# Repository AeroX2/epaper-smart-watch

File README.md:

# E-paper smart watch

- [Watch firmware](code/README.md)
- [Android companion](companion/README.md)

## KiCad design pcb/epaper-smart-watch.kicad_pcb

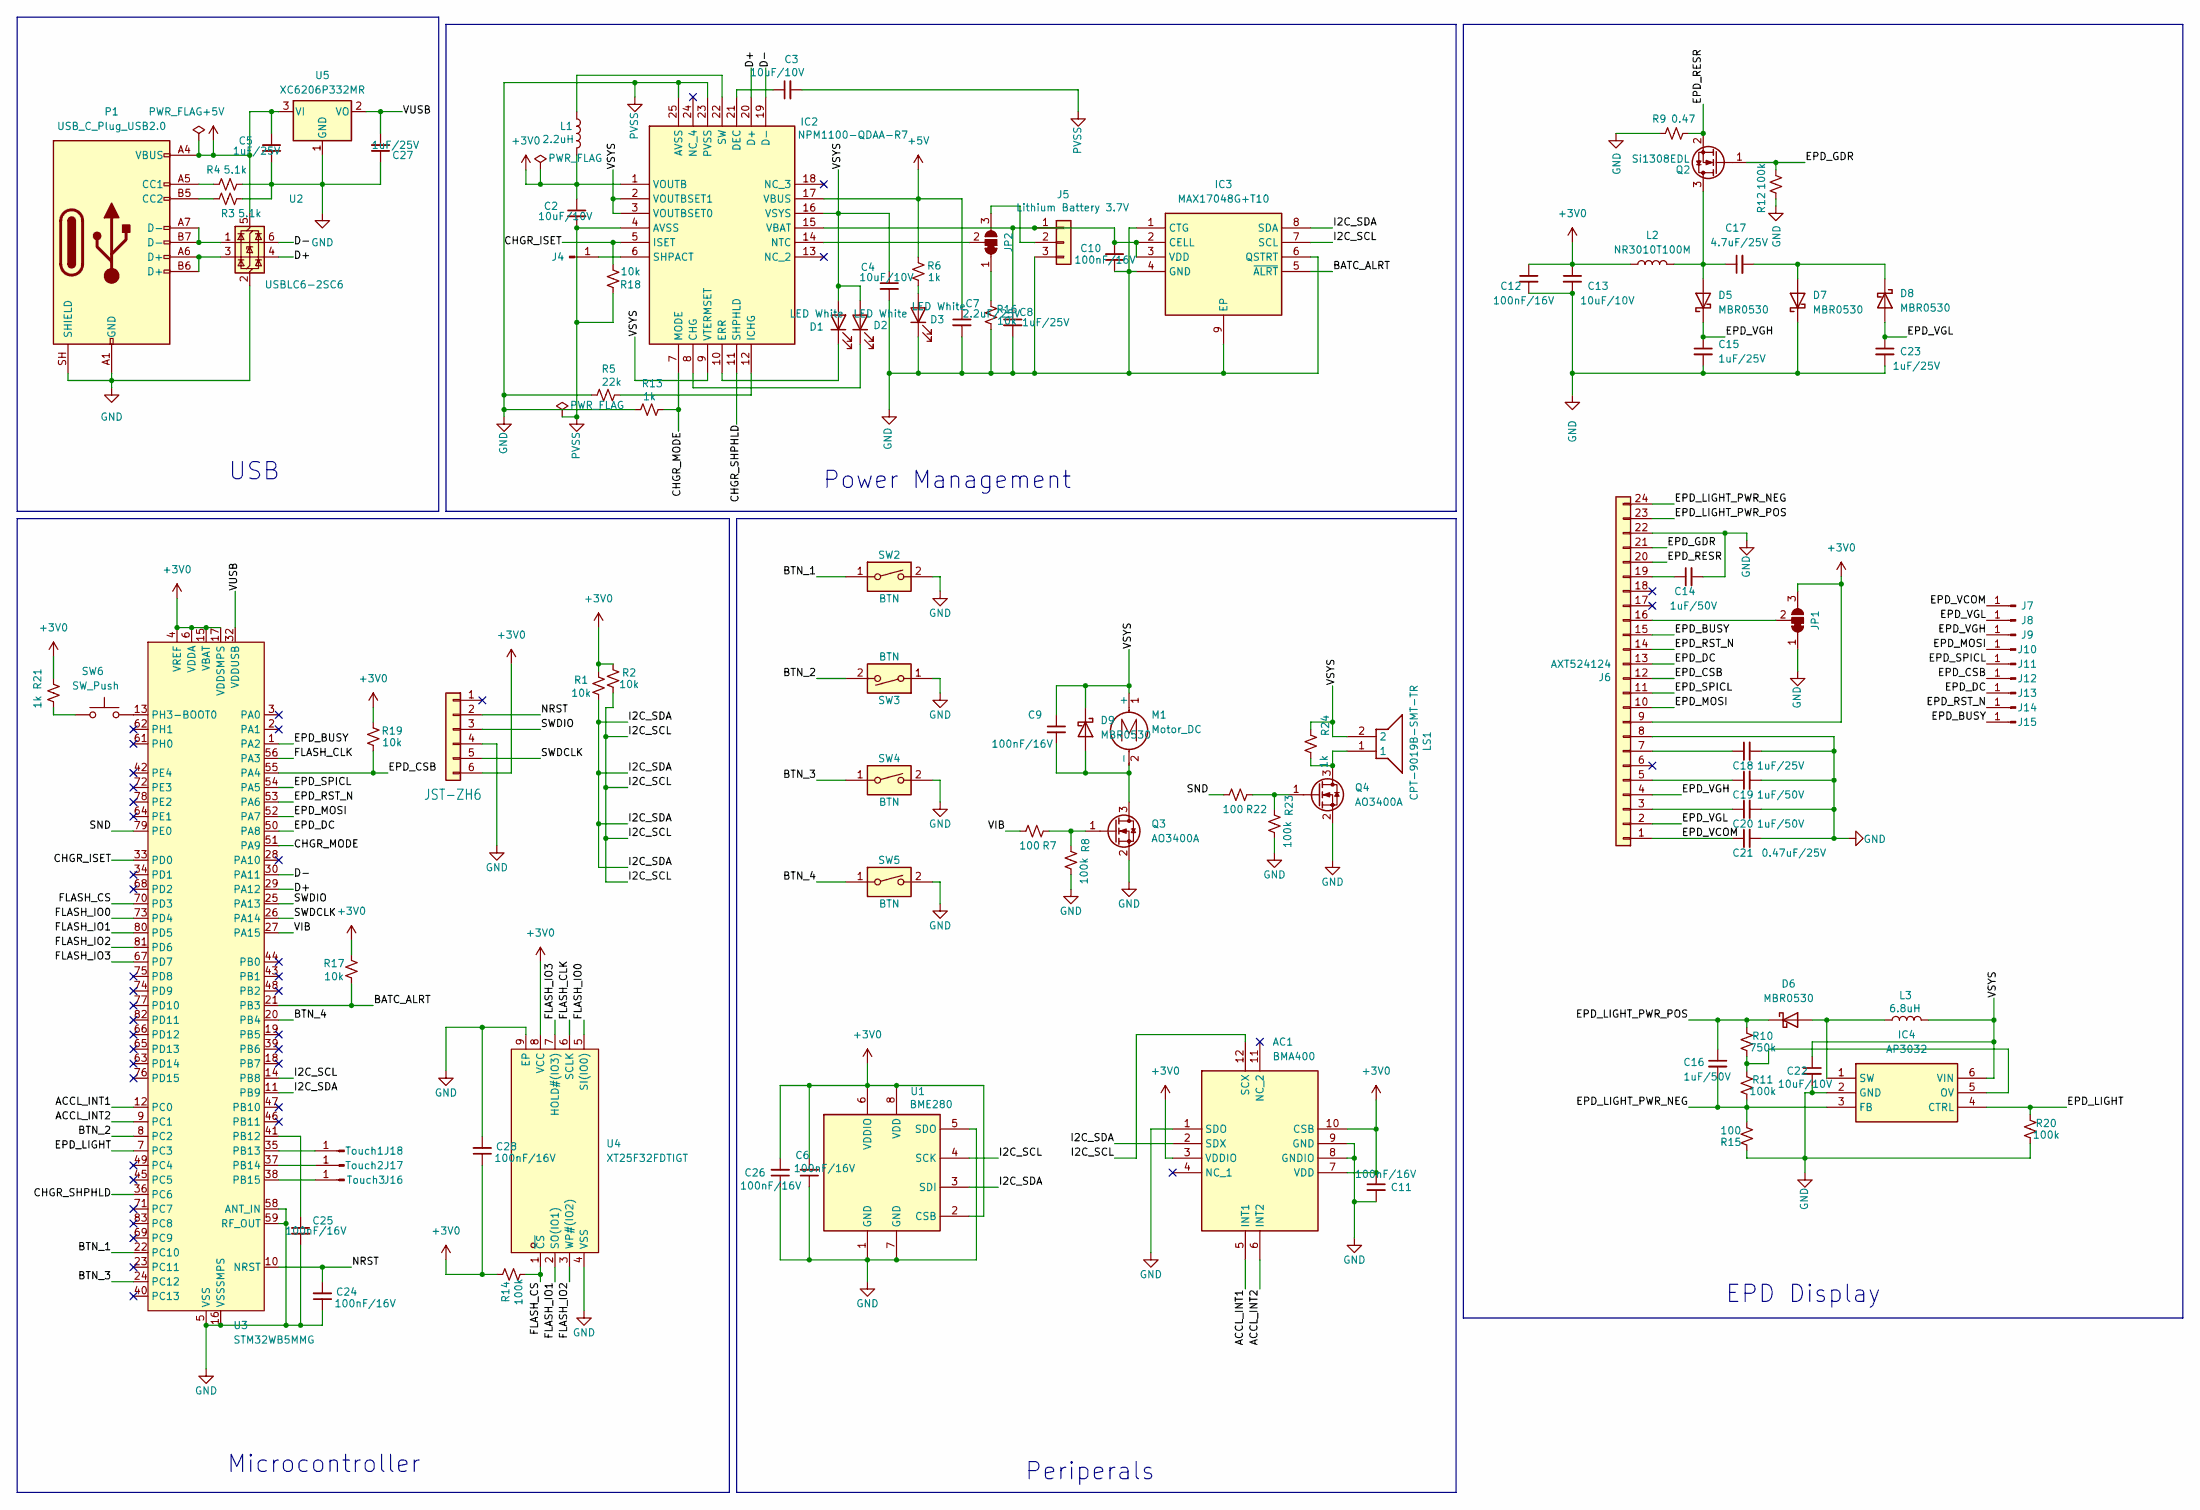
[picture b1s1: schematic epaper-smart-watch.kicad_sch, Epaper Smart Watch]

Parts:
AC1: BMA400; LGA-12_2x2mm_P0.5mm; Manufacturer_Part_Number BMA400; Mouser Part Number 262-BMA400
C2, C3, C4, C13, C22: 10uF/10V; C_0603_1608Metric; LCSC C19702
C5, C8, C18, C27: 1uF/25V; C_0402_1005Metric; LCSC C52923
C6, C9, C10, C11, C12, C24, C25, C26, C28: 100nF/16V; C_0402_1005Metric; LCSC C1525
C7: 2.2uF/25V; C_0805_2012Metric; LCSC C377773
C14, C16, C19, C20: 1uF/50V; C_0603_1608Metric; LCSC C15849
C15, C23: 1uF/25V; C_0805_2012Metric; LCSC C28323
C17: 4.7uF/25V; C_0805_2012Metric; LCSC C1779
C21: 0.47uF/25V; C_0603_1608Metric; LCSC C1623
D1, D2, D3: LED White; LED_0603_1608Metric; LCSC C2290
D5, D6, D7, D8, D9: MBR0530; D_SOD-123; LCSC C77336
IC2: NPM1100-QDAA-R7; QFN50P400X400X90-25N-D; Manufacturer_Part_Number NPM1100-QDAA-R7; Mouser Part Number 949-NPM1100-QDAA-R7
IC3: MAX17048G+T10; SON50P200X200X80-9N-D; Manufacturer_Part_Number MAX17048G+T10; Mouser Part Number 700-MAX17048G+T10
IC4: AP3032; SOT95P280X145-6N; Manufacturer_Part_Number AP3032; Mouser Part Number N/A
J4, J7, J8, J9, J10, J11, J12, J13, J14, J15: TestPoint_Pad_D1.0mm
J5: Lithium Battery 3.7V; SolderJumper-3_P1.3mm_Open_Pad1.0x1.5mm
J6: AXT524124; PANASONIC_AXT524124; LCSC C2859266
J16: Touch3; TestPoint_Pad_D1.0mm
J17: Touch2; TestPoint_Pad_D1.0mm
J18: Touch1; TestPoint_Pad_D1.0mm
JP1, JP2: SolderJumper_3_Bridged12; SolderJumper-3_P1.3mm_Bridged12_RoundedPad1.0x1.5mm_NumberL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
L1: 2.2uH; L_0603_1608Metric; LCSC C394950
L2: NR3010T100M; L_Taiyo-Yuden_NR-30xx; LCSC C6364771
L3: 6.8uH; L_0603_1608Metric; LCSC C50325627
LS1: CPT-9019B-SMT-TR; CPT9019SSMTTR; Manufacturer_Part_Number CPT-9019S-SMT-TR; Mouser Part Number 490-CPT-9019S-SMT-TR
M1: Motor_DC; SolderJumper-2_P1.3mm_Open_Pad1.0x1.5mm
P1: USB_C_Plug_USB2.0; USB-C-SMD_SHOU_TYPE-C-16P-CB1.6; LCSC C2906290
Q2: Si1308EDL; SOT-323_SC-70; LCSC C469327
Q3, Q4: AO3400A; SOT-23; LCSC C20917
R1, R2, R16, R17, R18, R19: 10k; R_0402_1005Metric; LCSC C25744
R3, R4: 5.1k; R_0402_1005Metric; LCSC C25905
R5: 22k; R_0402_1005Metric; LCSC C25768
R6, R13, R21, R24: 1k; R_0402_1005Metric; LCSC C11702
R7, R15, R22: 100; R_0402_1005Metric; LCSC C25076
R8, R11, R12, R14, R20, R23: 100k; R_0402_1005Metric; LCSC C25741
R9: 0.47; R_0402_1005Metric; LCSC C2090812
R10: 750k; R_0603_1608Metric; LCSC C23240
SW2, SW3, SW4, SW5: BTN; SW_SPST_B3U-3000P; LCSC C963349
SW6: SW_Push; SW_SPST_TS-1088-xR020; LCSC C720477
SWD1: JST-ZH6; JST_ZE_SM06B-ZESS-TB_1x06-1MP_P1.50mm_Horizontal; MPN S6B-ZR-SM4A-TF(LF)(SN); LCSC C5306612
U1: BME280; Bosch_LGA-8_2.5x2.5mm_P0.65mm_ClockwisePinNumbering; LCSC C92489
U2: USBLC6-2SC6; SOT-23-6; LCSC C7519
U3: STM32WB5MMG; ST-SiP-LGA-86-11x7.3mm; LCSC C5184586
U4: XT25F32FDTIGT; DFN-8_L3.0-W2.0-P0.50-BL-EP_XT25XXX; MPN XT25F32FDTIGT; LCSC C7429719
U5: XC6206P332MR; SOT-23-3; LCSC C5446

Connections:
+3V0: AC1.3 (VDDIO), AC1.7 (VDD), AC1.10 (CSB), C2.1, C6.2, C11.1, C12.1, C13.1, C26.2, C28.1, IC2.1 (VOUTB), J6.9, JP1.3 (B), L1.2, L2.1, R1.1, R2.1, R14.1, R17.1, R19.1, R21.1, SWD1.6, U1.2 (CSB), U1.6 (VDDIO), U1.8 (VDD), U3.4 (VREF), U3.6 (VDDA), U3.15 (VBAT), U3.17 (VDDSMPS), U4.8 (VCC)
+5V: C5.1, C7.1, IC2.17 (VBUS), P1.A4 (VBUS), P1.A9 (VBUS), P1.B4 (VBUS), P1.B9 (VBUS), R6.1, U2.5 (VBUS), U5.3 (VI)
/ACCL_INT1: AC1.5 (INT1), U3.12 (PC0)
/ACCL_INT2: AC1.6 (INT2), U3.9 (PC1)
/BATC_ALRT: IC3.5 (~ALRT), R17.2, U3.21 (PB3)
/BTN_1: SW2.1, U3.22 (PC10)
/BTN_2: SW3.2, U3.8 (PC2)
/BTN_3: SW4.1, U3.24 (PC12)
/BTN_4: SW5.1, U3.20 (PB4)
/CHGR_ISET: IC2.5 (ISET), R18.2, U3.33 (PD0)
/CHGR_MODE: IC2.7 (MODE), R13.2, U3.51 (PA9)
/CHGR_SHPHLD: IC2.11 (SHPHLD), U3.36 (PC6)
/D+: IC2.20 (D+), U2.4 (I/O2), U3.29 (PA12)
/D-: IC2.19 (D-), U2.6 (I/O1), U3.30 (PA11)
/EPD_BUSY: J6.15, J15.1 (Pin_1_1), U3.1 (PA2)
/EPD_CSB: J6.12, J12.1 (Pin_1_1), R19.2, U3.55 (PA4)
/EPD_DC: J6.13, J13.1 (Pin_1_1), U3.50 (PA8)
/EPD_GDR: J6.21, Q2.1 (G), R12.2
/EPD_LIGHT: IC4.4 (CTRL), R20.1, U3.7 (PC3)
/EPD_LIGHT_PWR_NEG: C16.2, IC4.3 (FB), J6.24, R11.2, R15.2
/EPD_LIGHT_PWR_POS: C16.1, D6.1 (K), J6.23, R10.1
/EPD_MOSI: J6.10, J10.1 (Pin_1_1), U3.52 (PA7)
/EPD_RESR: J6.20, Q2.2 (S), R9.2
/EPD_RST_N: J6.14, J14.1 (Pin_1_1), U3.53 (PA6)
/EPD_SPICL: J6.11, J11.1 (Pin_1_1), U3.54 (PA5)
/EPD_VCOM: C21.1, J6.1, J7.1 (Pin_1_1)
/EPD_VGH: C15.1, D5.1 (K), J6.4, J9.1 (Pin_1_1)
/EPD_VGL: C23.1, D8.2 (A), J6.2, J8.1 (Pin_1_1)
/FLASH_CLK: U3.56 (PA3), U4.6 (SCLK)
/FLASH_CS: R14.2, U3.70 (PD3), U4.1 (~CS)
/FLASH_IO0: U3.73 (PD4), U4.5 (SI(IO0))
/FLASH_IO1: U3.80 (PD5), U4.2 (SO(IO1))
/FLASH_IO2: U3.81 (PD6), U4.3 (WP#(IO2))
/FLASH_IO3: U3.67 (PD7), U4.7 (HOLD#(IO3))
/I2C_SCL: AC1.12 (SCX), IC3.7 (SCL), R2.2, U1.4 (SCK), U3.14 (PB8)
/I2C_SDA: AC1.2 (SDX), IC3.8 (SDA), R1.2, U1.3 (SDI), U3.11 (PB9)
/NRST: C24.2, SWD1.2, U3.10 (NRST)
/SND: R22.2, U3.79 (PE0)
/SWDCLK: SWD1.5, U3.26 (PA14)
/SWDIO: SWD1.3, U3.25 (PA13)
/VIB: R7.2, U3.27 (PA15)
/VSYS: C4.1, C9.1, C22.1, D1.2 (A), D2.2 (A), D9.1 (K), IC2.2 (VOUTBSET1), IC2.3 (VOUTBSET0), IC2.9 (VTERMSET), IC2.16 (VSYS), IC4.6 (VIN), L3.2, LS1.2, M1.1 (+), R24.1
/VUSB: C27.2, U3.32 (VDDUSB), U5.2 (VO)
GND: AC1.1 (SDO), AC1.8 (GNDIO), AC1.9 (GND), C2.2, C3.2, C4.2, C5.2, C6.1, C7.2, C8.2, C10.2, C11.2, C12.2, C13.2, C14.2, C15.2, C18.2, C19.2, C20.2, C21.2, C22.2, C23.2, C24.1, C25.2, C26.1, C27.1, C28.2, D3.1 (K), D7.1 (K), IC2.4 (AVSS), IC2.23 (PVSS), IC2.25 (AVSS), IC3.1 (CTG), IC3.4 (GND), IC3.6 (QSTRT), IC3.9 (EP), IC4.2 (GND), J5.3, J6.8, J6.22, JP1.1 (A), P1.A1 (GND), P1.A12 (GND), P1.B1 (GND), P1.B12 (GND), P1.SH (SHIELD), Q3.2 (S), Q4.2 (S), R3.1, R4.1, R5.1, R8.2, R9.1, R12.1, R13.1, R15.1, R16.2, R18.1, R20.2, R23.2, SW2.2, SW3.1, SW4.2, SW5.2, SWD1.4, U1.1 (GND), U1.5 (SDO), U1.7 (GND), U2.2 (GND), U3.5 (VSS), U3.16 (VSSSMPS), U3.31 (VSS), U3.57 (VSS), U3.58 (ANT_IN), U3.59 (RF_OUT), U3.60 (VSS), U3.84 (VSS), U3.86 (VSS), U4.4 (VSS), U4.9 (EP), U5.1 (GND)
unnamed: D1.1 (K), IC2.10 (ERR)
unnamed: D2.1 (K), IC2.8 (CHG)
unnamed: D3.2 (A), R6.2
unnamed: C17.1, D5.2 (A), L2.2, Q2.3 (D)
unnamed: D6.2 (A), IC4.1 (SW), L3.1
unnamed: C17.2, D7.2 (A), D8.1 (K)
unnamed: C9.2, D9.2 (A), M1.2 (-), Q3.3 (D)
unnamed: C3.1, IC2.21 (DEC)
unnamed: IC2.12 (ICHG), R5.2
unnamed: IC2.14 (NTC), JP2.2 (C)
unnamed: IC2.6 (SHPACT), J4.1 (Pin_1_1)
unnamed: IC2.22 (SW), L1.1
unnamed: C8.1, C10.1, IC2.15 (VBAT), IC3.2 (CELL), IC3.3 (VDD), J5.1
unnamed: IC4.5 (OV), R10.2, R11.1
unnamed: J5.2, JP2.3 (B)
unnamed: C20.1, J6.3
unnamed: C19.1, J6.5
unnamed: C18.1, J6.7
unnamed: J6.16, JP1.2 (C)
unnamed: C14.1, J6.19
unnamed: J16.1 (Pin_1_1), U3.38 (PB15)
unnamed: J17.1 (Pin_1_1), U3.37 (PB14)
unnamed: J18.1 (Pin_1_1), U3.35 (PB13)
unnamed: JP2.1 (A), R16.1
unnamed: P1.A5 (CC1), R4.2
unnamed: P1.B5 (CC2), R3.2
unnamed: P1.A6 (D+), P1.B6 (D+), U2.3 (I/O2)
unnamed: P1.A7 (D-), P1.B7 (D-), U2.1 (I/O1)
unnamed: Q3.1 (G), R7.1, R8.1
unnamed: LS1.1, Q4.3 (D), R24.2
unnamed: Q4.1 (G), R22.1, R23.1
unnamed: R21.2, SW6.1
unnamed: C25.1, U3.41 (PB12)
unnamed: SW6.2, U3.13 (PH3-BOOT0)

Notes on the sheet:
USB
Power Management
EPD Display
Periperals
Microcontroller

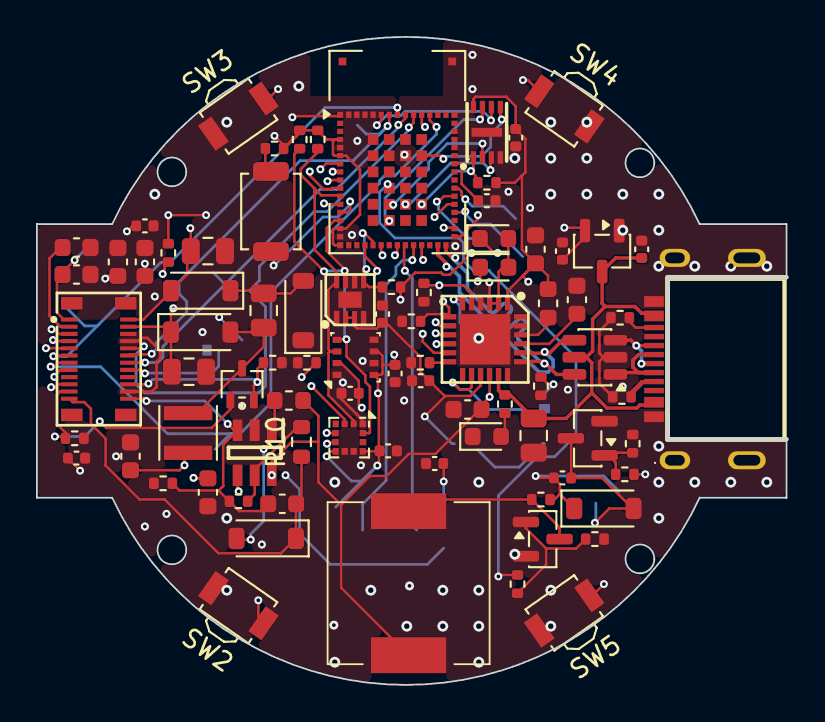
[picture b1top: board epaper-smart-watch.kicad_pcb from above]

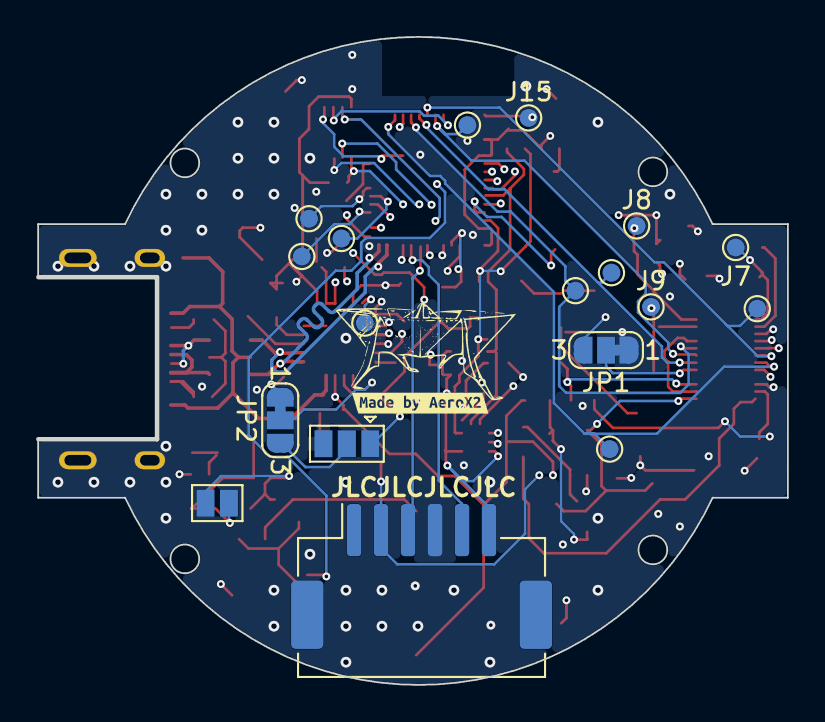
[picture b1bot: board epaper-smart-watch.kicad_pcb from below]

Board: 4 copper layers, 41.6 x 36.0 mm, 101 parts (19 on the bottom side), 78 nets.

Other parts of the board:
kibuzzard-6782824E: G***; kibuzzard-6782824E

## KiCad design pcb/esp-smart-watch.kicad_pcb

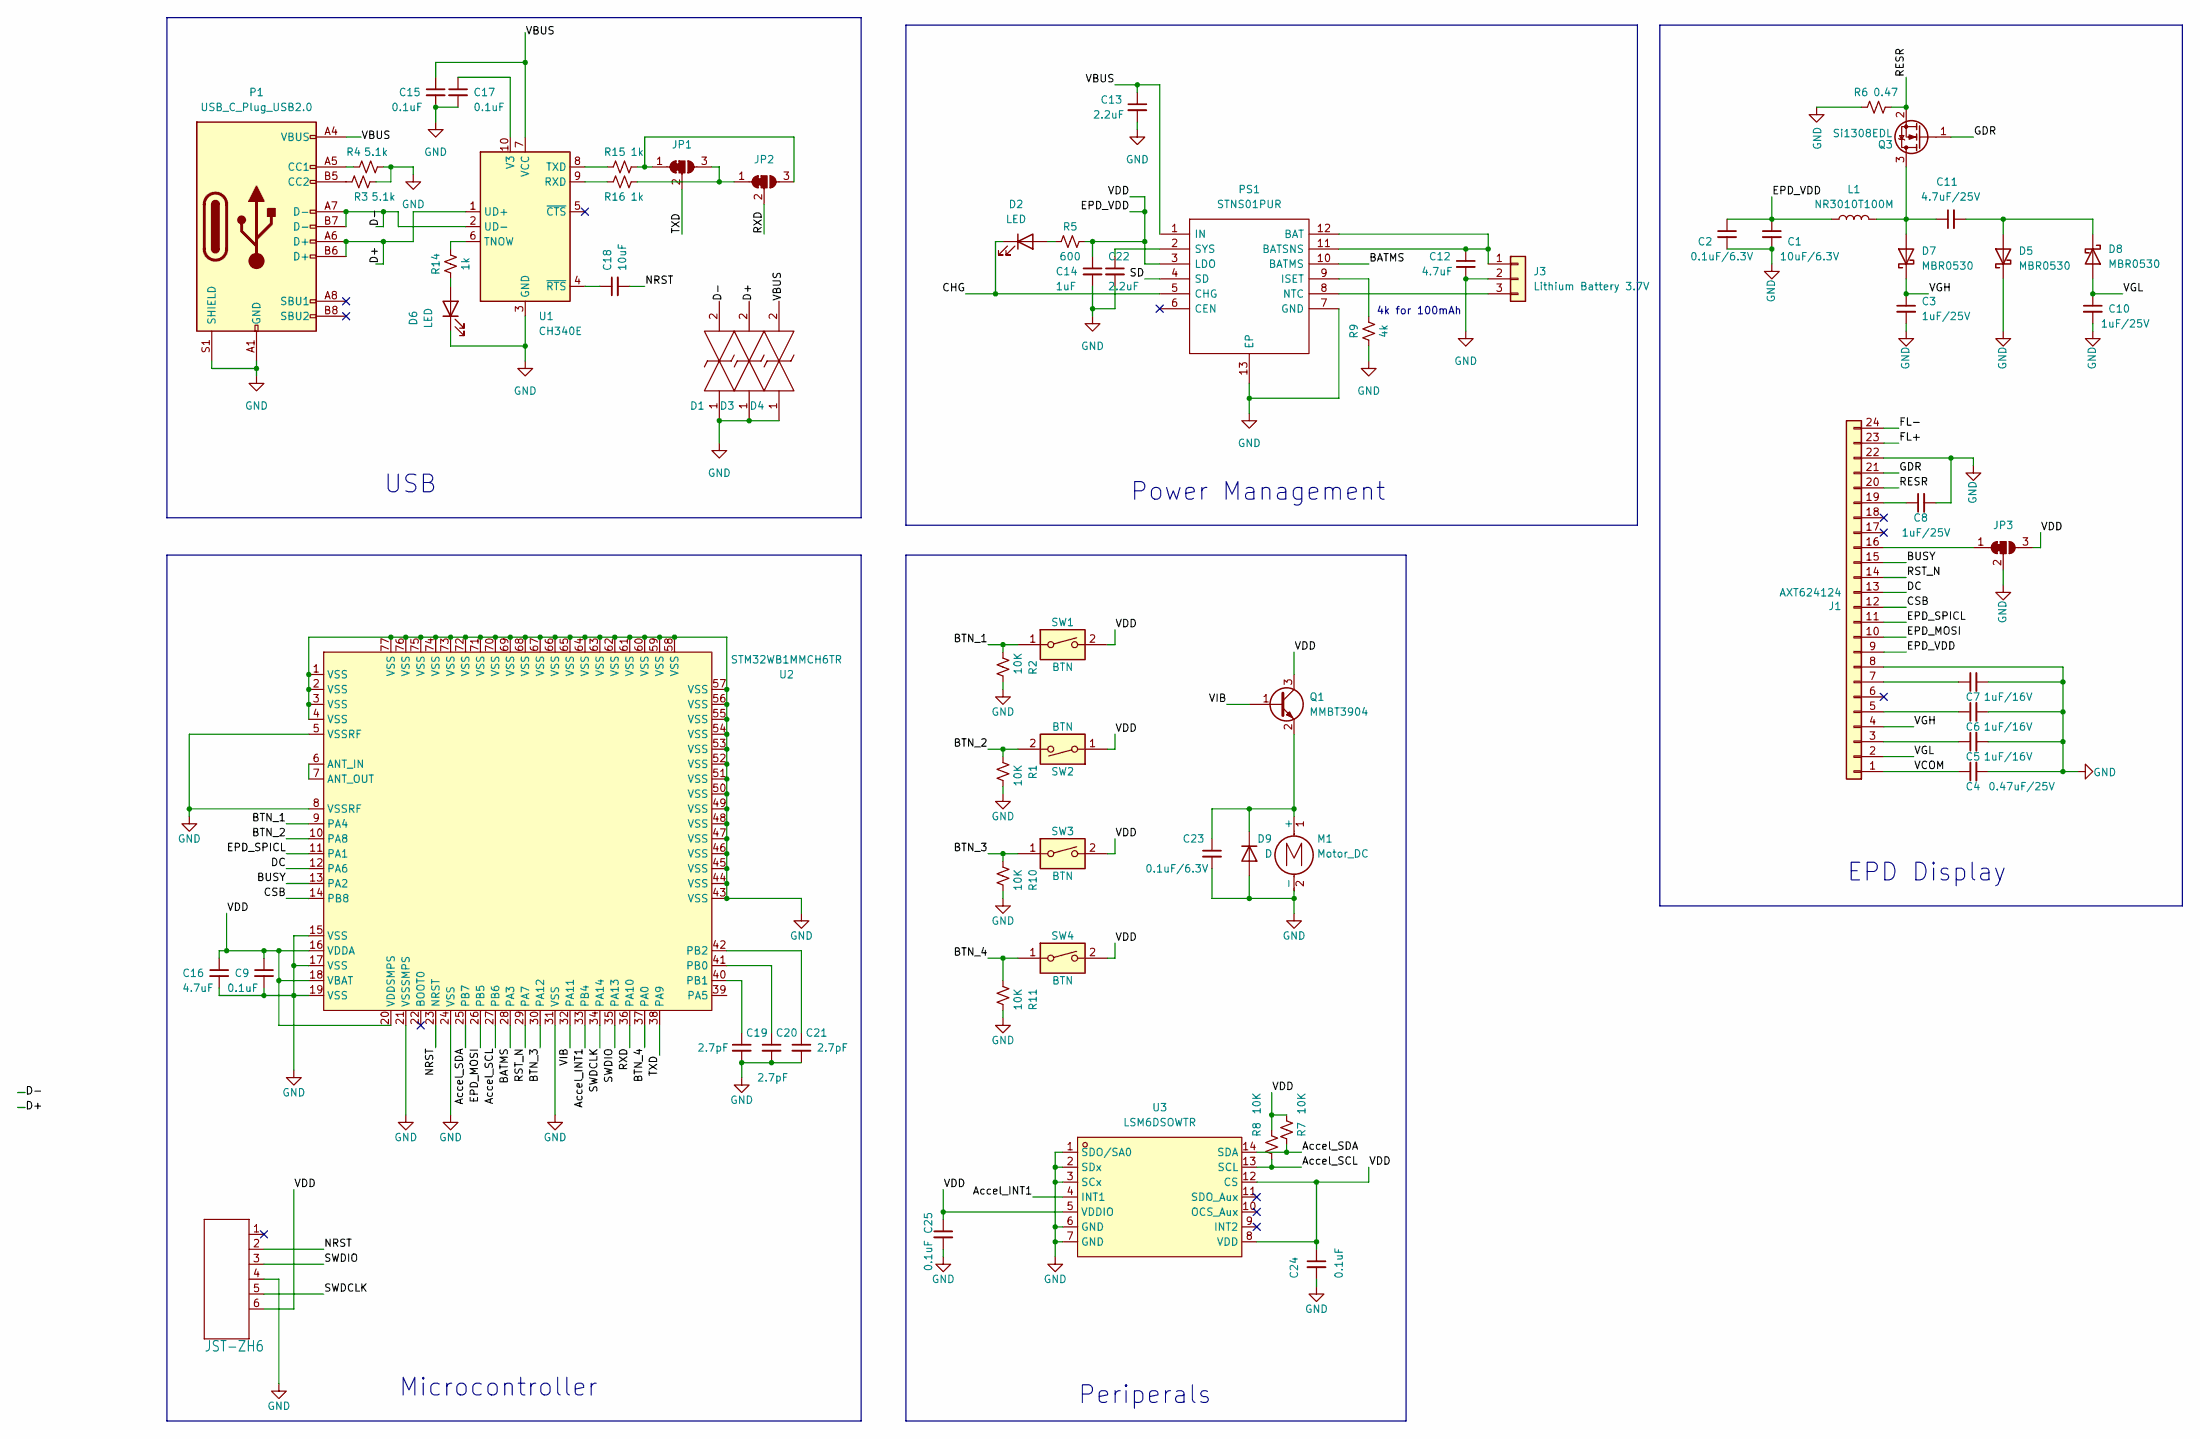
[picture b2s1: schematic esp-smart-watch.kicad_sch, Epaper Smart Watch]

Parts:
C1: 10uF/6.3V; C_0402_1005Metric
C2, C23: 0.1uF/6.3V; C_0402_1005Metric
C3, C10: 1uF/25V; C_0805_2012Metric
C4: 0.47uF/25V; C_0402_1005Metric
C5, C6, C7: 1uF/16V; C_0402_1005Metric
C8: 1uF/25V; C_0402_1005Metric
C9: 0.1uF; C_0402_1005Metric; Manufacturer Part CC0402KRX7R6BB104
C11: 4.7uF/25V; C_0805_2012Metric
C12: 4.7uF; C_0402_1005Metric
C13, C22: 2.2uF; C_0402_1005Metric
C14: 1uF; C_0402_1005Metric
C15, C17: 0.1uF; C_0402_1005Metric; Manufacturer Part GRM188R61C475KE11D
C16: 4.7uF; C_0402_1005Metric; Manufacturer Part GRM188R61C475KE11D
C18: 10uF; C_0402_1005Metric; Manufacturer Part GRM188R61C475KE11D
C19, C20, C21: 2.7pF; C_0402_1005Metric; Manufacturer Part GRM188R61C475KE11D
C24, C25: 0.1uF; C_0402_1005Metric
D1, D3, D4: LESD5D5.0CT1G; LESD5D50CT1G; Manufacturer_Part_Number LESD5D5.0CT1G; LCSC C383211
D2, D6: LED; LED_0402_1005Metric
D5, D7, D8: MBR0530; D_SOD-123
D9: D; D_0402_1005Metric
J1: AXT624124
J3: Lithium Battery 3.7V; SolderJumper-3_P1.3mm_Open_Pad1.0x1.5mm
JP1, JP2, JP3: SolderJumper_3_Bridged12; SolderJumper-3_P1.3mm_Bridged12_RoundedPad1.0x1.5mm_NumberL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
L1: NR3010T100M; L_Taiyo-Yuden_NR-40xx
M1: Motor_DC; SolderJumper-2_P1.3mm_Open_Pad1.0x1.5mm
P1: USB_C_Plug_USB2.0; USB-C-SMD_KH-TYPE-C-16P
PS1: STNS01PUR; SON45P300X300X80-13N-D; Manufacturer_Part_Number STNS01PUR; Mouser Part Number 511-STNS01PUR
Q1: MMBT3904; SOT-23
Q3: Si1308EDL; SOT-323_SC-70
R1, R2, R7, R8, R10, R11: 10K; R_0402_1005Metric
R3, R4: 5.1k; R_0402_1005Metric
R5: 600; R_0402_1005Metric
R6: 0.47; R_0402_1005Metric
R9: 4k; R_0402_1005Metric
R14, R15, R16: 1k; R_0402_1005Metric
SW1, SW2, SW3, SW4: BTN; SW_SPST_B3U-3000P-B
SWD1: JST-ZH6; JST_ZE_SM06B-ZESS-TB_1x06-1MP_P1.50mm_Horizontal; MPN S6B-ZR-SM4A-TF(LF)(SN)
U1: CH340E; MSOP-10_3x3mm_P0.5mm
U2: STM32WB1MMCH6TR; LGA-77_L10.0-W6.5-STM32WB1MMCH6TR; LCSC Part C5456183
U3: LSM6DSOWTR; LGA-14L_L3.0-W2.5-P0.50-TL; LCSC Part C2829074

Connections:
/Accel_INT1: U2.33 (PB4), U3.4 (INT1)
/Accel_SCL: R8.2, U2.27 (PB6), U3.13 (SCL)
/Accel_SDA: R7.2, U2.25 (PB7), U3.14 (SDA)
/BATMS: PS1.10 (BATMS), U2.28 (PA3)
/BTN_1: R2.2, SW1.1, U2.9 (PA4)
/BTN_2: R1.2, SW2.2, U2.10 (PA8)
/BTN_3: R10.2, SW3.1, U2.30 (PA12)
/BTN_4: R11.2, SW4.1, U2.37 (PA0)
/BUSY: J1.15, U2.13 (PA2)
/CHG: D2.1 (K), PS1.5 (CHG)
/CSB: J1.12, U2.14 (PB8)
/D+: D3.2, P1.A6 (D+), P1.B6 (D+), U1.1 (UD+)
/D-: D1.2, P1.A7 (D-), P1.B7 (D-), U1.2 (UD-)
/DC: J1.13, U2.12 (PA6)
/EPD_MOSI: J1.10, U2.26 (PB5)
/EPD_SPICL: J1.11, U2.11 (PA1)
/EPD_VDD: C1.1, C2.1, C9.1, C14.1, C16.1, C24.1, C25.1, J1.9, JP3.3 (B), L1.1, PS1.3 (LDO), Q1.3 (C), R5.1, R7.1, R8.1, SW1.2, SW2.1, SW3.2, SW4.2, SWD1.6, U2.16 (VDDA), U2.18 (VBAT), U2.20 (VDDSMPS), U3.5 (VDDIO), U3.8 (VDD), U3.12 (CS)
/FL+: J1.23
/FL-: J1.24
/GDR: J1.21, Q3.1 (G)
/NRST: C18.2, SWD1.2, U2.23 (NRST)
/RESR: J1.20, Q3.2 (S), R6.2
/RST_N: J1.14, U2.29 (PA7)
/RXD: JP2.2 (C), U2.36 (PA10)
/SD: PS1.4 (SD)
/SWDCLK: SWD1.5, U2.34 (PA14)
/SWDIO: SWD1.3, U2.35 (PA13)
/TXD: JP1.2 (C), U2.38 (PA9)
/VBUS: C13.1, C15.1, D4.2, P1.A4 (VBUS), P1.A9 (VBUS), P1.B4 (VBUS), P1.B9 (VBUS), PS1.1 (IN), U1.7 (VCC)
/VCOM: C4.1, J1.1
/VGH: C3.1, D7.1 (K), J1.4
/VGL: C10.1, D8.2 (A), J1.2
/VIB: Q1.1 (B), U2.32 (PA11)
GND: C1.2, C2.2, C3.2, C4.2, C5.2, C6.2, C7.2, C8.2, C9.2, C10.2, C12.2, C13.2, C14.2, C15.2, C16.2, C17.2, C19.2, C20.2, C21.2, C22.2, C23.2, C24.2, C25.2, D1.1, D3.1, D4.1, D5.1 (K), D6.1 (K), D9.2 (A), J1.8, J1.22, J3.2, JP3.2 (C), M1.2 (-), P1.A1 (GND), P1.A12 (GND), P1.B1 (GND), P1.B12 (GND), P1.S1 (SHIELD), PS1.7 (GND), PS1.13 (EP), R1.1, R2.1, R3.1, R4.1, R6.1, R9.2, R10.1, R11.1, SWD1.4, U1.3 (GND), U2.1 (VSS), U2.2 (VSS), U2.3 (VSS), U2.4 (VSS), U2.5 (VSSRF), U2.8 (VSSRF), U2.15 (VSS), U2.17 (VSS), U2.19 (VSS), U2.21 (VSSSMPS), U2.24 (VSS), U2.31 (VSS), U2.43 (VSS), U2.44 (VSS), U2.45 (VSS), U2.46 (VSS), U2.47 (VSS), U2.48 (VSS), U2.49 (VSS), U2.50 (VSS), U2.51 (VSS), U2.52 (VSS), U2.53 (VSS), U2.54 (VSS), U2.55 (VSS), U2.56 (VSS), U2.57 (VSS), U2.58 (VSS), U2.59 (VSS), U2.60 (VSS), U2.61 (VSS), U2.62 (VSS), U2.63 (VSS), U2.64 (VSS), U2.65 (VSS), U2.66 (VSS), U2.67 (VSS), U2.68 (VSS), U2.69 (VSS), U2.70 (VSS), U2.71 (VSS), U2.72 (VSS), U2.73 (VSS), U2.74 (VSS), U2.75 (VSS), U2.76 (VSS), U2.77 (VSS), U3.1 (SDO/SA0), U3.2 (SDx), U3.3 (SCx), U3.6 (GND), U3.7 (GND)
unnamed: D2.2 (A), R5.2
unnamed: C11.2, D5.2 (A), D8.1 (K)
unnamed: D6.2 (A), R14.2
unnamed: C11.1, D7.2 (A), L1.2, Q3.3 (D)
unnamed: C23.1, D9.1 (K), M1.1 (+), Q1.2 (E)
unnamed: C5.1, J1.3
unnamed: C6.1, J1.5
unnamed: C7.1, J1.7
unnamed: J1.16, JP3.1 (A)
unnamed: C8.1, J1.19
unnamed: C12.1, J3.1, PS1.11 (BATSNS), PS1.12 (BAT)
unnamed: J3.3, PS1.8 (NTC)
unnamed: JP1.1 (A), JP2.3 (B), R15.2
unnamed: JP1.3 (B), JP2.1 (A), R16.2
unnamed: P1.A5 (CC1), R4.2
unnamed: P1.B5 (CC2), R3.2
unnamed: PS1.9 (ISET), R9.1
unnamed: C22.1, PS1.2 (SYS)
unnamed: R16.1, U1.9 (RXD)
unnamed: R14.1, U1.6 (TNOW)
unnamed: R15.1, U1.8 (TXD)
unnamed: C17.1, U1.10 (V3)
unnamed: C18.1, U1.4 (~RTS)
unnamed: U2.6 (ANT_IN), U2.7 (ANT_OUT)
unnamed: C20.1, U2.41 (PB0)
unnamed: C19.1, U2.40 (PB1)
unnamed: C21.1, U2.42 (PB2)

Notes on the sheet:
USB
Power Management
EPD Display
Periperals
Microcontroller
4k for 100mAh

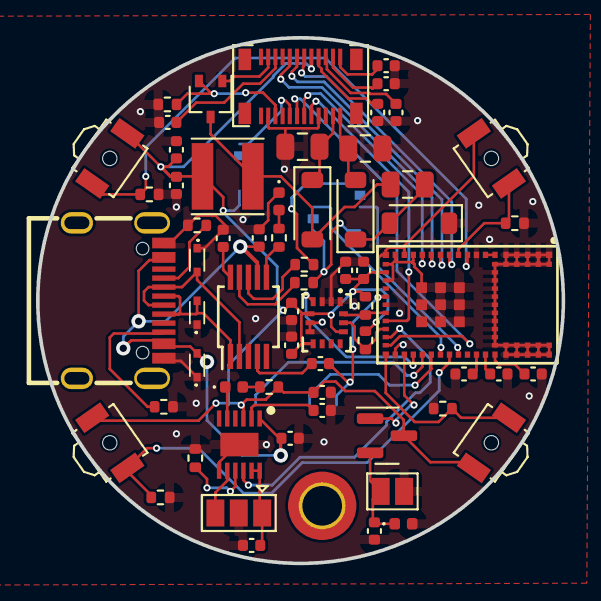
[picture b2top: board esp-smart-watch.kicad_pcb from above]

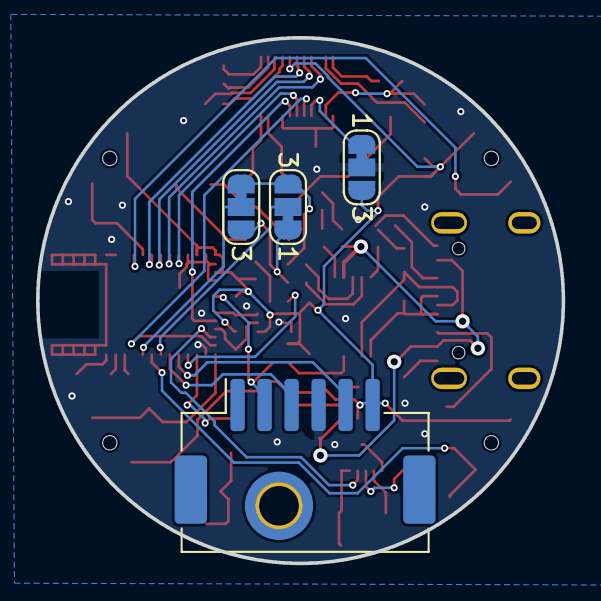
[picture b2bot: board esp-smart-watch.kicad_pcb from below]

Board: 4 copper layers, 29.2 x 29.2 mm, 67 parts (4 on the bottom side), 58 nets.

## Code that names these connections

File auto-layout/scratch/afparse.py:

import re, xml.etree.ElementTree as ET
F = r"C:\Program Files\STMicroelectronics\STM32Cube\STM32CubeMX\db\mcu\IP\GPIO-STM32WB5Mx_gpio_v1_0_Modes.xml"
raw = open(F, encoding='utf-8').read()
# strip namespace for easy parsing
raw = re.sub(r'\sxmlns(:\w+)?="[^"]+"', '', raw)
raw = re.sub(r'ns0:', '', raw)
root = ET.fromstring(raw)

pin2sig = {}   # pin -> list of (signal, af)
sig2pin = {}   # signal -> list of (pin, af)
for gp in root.findall('.//GPIO_Pin'):
    pin = gp.get('Name')
    for ps in gp.findall('PinSignal'):
        sig = ps.get('Name')
        af = None
        pv = ps.find('.//PossibleValue')
        if pv is not None and pv.text and pv.text.startswith('GPIO_AF'):
            m = re.match(r'GPIO_AF(\d+)_', pv.text)
            af = int(m.group(1)) if m else None
        pin2sig.setdefault(pin, []).append((sig, af))
        sig2pin.setdefault(sig, []).append((pin, af))

# Module-exposed pins (from netlist U4 pin map) and which are FREE right now
exposed = set("""PA0 PA1 PA2 PA3 PA4 PA5 PA6 PA7 PA8 PA9 PA10 PA11 PA12 PA13 PA14 PA15
PB2 PB3 PB4 PB5 PB6 PB7 PB8 PB9 PB10 PB11 PB12 PB13 PB14 PB15
PC0 PC1 PC2 PC3 PC4 PC5 PC6 PC7 PC8 PC9 PC10 PC11 PC12 PC13
PD0 PD1 PD2 PD3 PD4 PD5 PD6 PD7 PD8 PD9 PD10 PD11 PD12 PD13 PD14 PD15
PE0 PE1 PE2 PE3 PE4 PH0 PH1""".split())
used = {  # pin: current function (from netlist)
 'PA2':'FLASH_CS','PA3':'FLASH_CLK','PA6':'FLASH_IO2','PA7':'FLASH_IO3','PB9':'FLASH_IO0','PB8':'FLASH_IO1',
 'PA4':'EPD_CSB','PA5':'EPD_SPICL','PA8':'EPD_DC',
 'PC1':'Accel_INT1','PC0':'Accel_INT2','PA15':'VIB(motor)',
 'PC10':'BTN1','PC11':'BTN2','PC12':'BTN3','PB4':'BTN4',
 'PA13':'SWDIO','PA14':'SWCLK','PA12':'USB_DP','PA11':'USB_DM',
 'PD0':'CHGR_ISET','PD1':'CHGR_MODE','PC6':'CHGR_SHPHLD',
 'PB14':'TOUCH(J2)','PB13':'TOUCH(J4)','PB12':'TOUCH(J5)',
 'PB10':'cap C25','PB11':'cap C26','PC5':'cap C22','PB15':'cap C19',
}
free = sorted(exposed - set(used), key=lambda p:(p[1], int(p[2:])))

def opts(signal, only_free=True):
    out=[]
    for pin,af in sig2pin.get(signal,[]):
        if pin in exposed and (not only_free or pin in free):
            out.append(f"{pin}(AF{af})")
    return out

print("FREE module pins:", ", ".join(free))
print()
for s in ['SPI1_SCK','SPI1_MISO','SPI1_MOSI','SPI1_NSS',
          'SPI2_SCK','SPI2_MISO','SPI2_MOSI','SPI2_NSS',
          'QUADSPI_CLK','QUADSPI_BK1_NCS','QUADSPI_BK1_IO0','QUADSPI_BK1_IO1','QUADSPI_BK1_IO2','QUADSPI_BK1_IO3',
          'I2C1_SCL','I2C1_SDA','I2C3_SCL','I2C3_SDA',
          'TIM1_CH1','TIM1_CH2','TIM1_CH3','TIM2_CH1','TIM2_CH2','TIM2_CH3','TIM2_CH4',
          'TIM16_CH1','TIM17_CH1','LPTIM1_OUT','LPTIM2_OUT']:
    allp = [f"{p}(AF{a})" for p,a in sig2pin.get(s,[]) if p in exposed]
    freep = opts(s)
    print(f"{s:18} free: {', '.join(freep) if freep else '-':45} | all: {', '.join(allp)}")

print("\n-- QUADSPI full (verify IO2/IO3) --")
for s in ['QUADSPI_BK1_IO2','QUADSPI_BK1_IO3']:
    print(s, [f"{p}(AF{a})" for p,a in sig2pin.get(s,[]) if p in exposed])
print("\n-- is PA15 a timer pin? --")
print('PA15:', [x for x in pin2sig.get('PA15',[]) if 'TIM' in x[0]])

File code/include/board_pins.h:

#pragma once

#include <Arduino.h>

namespace BoardPins {

// Shared I2C1 bus.
constexpr uint32_t I2C_SDA = PB9;
constexpr uint32_t I2C_SCL = PB8;

// Sensor and fuel-gauge interrupt inputs.
constexpr uint32_t ACCEL_INT1 = PC0;
constexpr uint32_t ACCEL_INT2 = PC1;
constexpr uint32_t BATTERY_ALERT = PB3;

// Active-low user buttons.
constexpr uint32_t BUTTON_1 = PC10;
constexpr uint32_t BUTTON_2 = PC2;
constexpr uint32_t BUTTON_3 = PC12;
constexpr uint32_t BUTTON_4 = PB4;

// nPM1100 control pins. Keep ISET low until USB current has been negotiated.
constexpr uint32_t CHARGER_ISET = PD0;
constexpr uint32_t CHARGER_MODE = PA9;
constexpr uint32_t SHIP_HOLD = PC6;

// Low-side actuator FET gates.
constexpr uint32_t VIBRATION = PA15;
constexpr uint32_t BUZZER = PE0;

// ET011TJ1 four-wire SPI interface. The display SDA line is write-only here.
constexpr uint32_t DISPLAY_SCK = PA5;
constexpr uint32_t DISPLAY_MOSI = PA7;
// The STM32 Arduino SPI core requires a valid MISO pin even for transmit-only
// buses. PB4 is physically button 4, not connected to the display data line,
// and is used only to let the core initialize SPI1.
constexpr uint32_t DISPLAY_DUMMY_MISO = PB4;
constexpr uint32_t DISPLAY_CS = PA4;
constexpr uint32_t DISPLAY_DC = PA8;
constexpr uint32_t DISPLAY_RESET = PA6;
constexpr uint32_t DISPLAY_BUSY = PA2;
constexpr uint32_t DISPLAY_LIGHT = PC3;

}  // namespace BoardPins

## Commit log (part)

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2024-11-09 Rename files
2024-11-11 Thickened power traces, fixed JP3 and removed pulldowns for buttons
2025-02-15 Use different accelerometer
2025-02-15 JLCPCB
2025-05-25 Initial code commit
2026-06-21 V2 soon...
